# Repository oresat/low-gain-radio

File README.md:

# OreSat "Low Gain Radio" board

## Overview

The Low Gain Radio module is part of the sputnik capstone project and is the communications pipeline for the CubeSat.  

The module is centered around a microcontroller with an integrated transceiver and RF front end. Commands will be sent and received through this module. In most cases the system controller will assist in executing those commands. Communication with the system controller is done via a UART connection between the two modules.

## Main Topics
[Parts Selection](https://github.com/oresat/low-gain-radio/blob/master/docs/Parts_Selection.md#parts-selection-for-low-gain-radio)  
[Bill of Materials](https://github.com/oresat/low-gain-radio/blob/master/docs/low-gain-radio_BOM.xlsx)  
[Eagle Schematic](https://github.com/oresat/low-gain-radio/blob/master/eagle/low-gain-radio.sch)    
[Eagle Layout](https://github.com/oresat/low-gain-radio/blob/master/eagle/low-gain-radio.brd)    
[Test Plan](https://github.com/oresat/low-gain-radio/blob/master/docs/Test_Plan_Sputnik_Capstone.md#sputnik-capstone-test-plan)    

## Contents

datasheets - datasheets for components used

docs - documentation

eagle - contains Schematic and PCB layout for the Low Gain Radio

tools - contains firmware and tools for compiling/debugging

## Project team

Industry Sponsor: Andrew Greenberg (adg@ece.pdx.edu)

Faculty Advisor: Dr. Christof Teuscher (teuscher@pdx.edu)

* Capstone Team
* 
    * Jake Heath (jakeheath@gmail.com)

    * Shan Quinney (quinney@pdx.edu) 

    * William Harrington (wrh2@pdx.edu)

    * Mike Mathis (mdmathis@gmail.com)

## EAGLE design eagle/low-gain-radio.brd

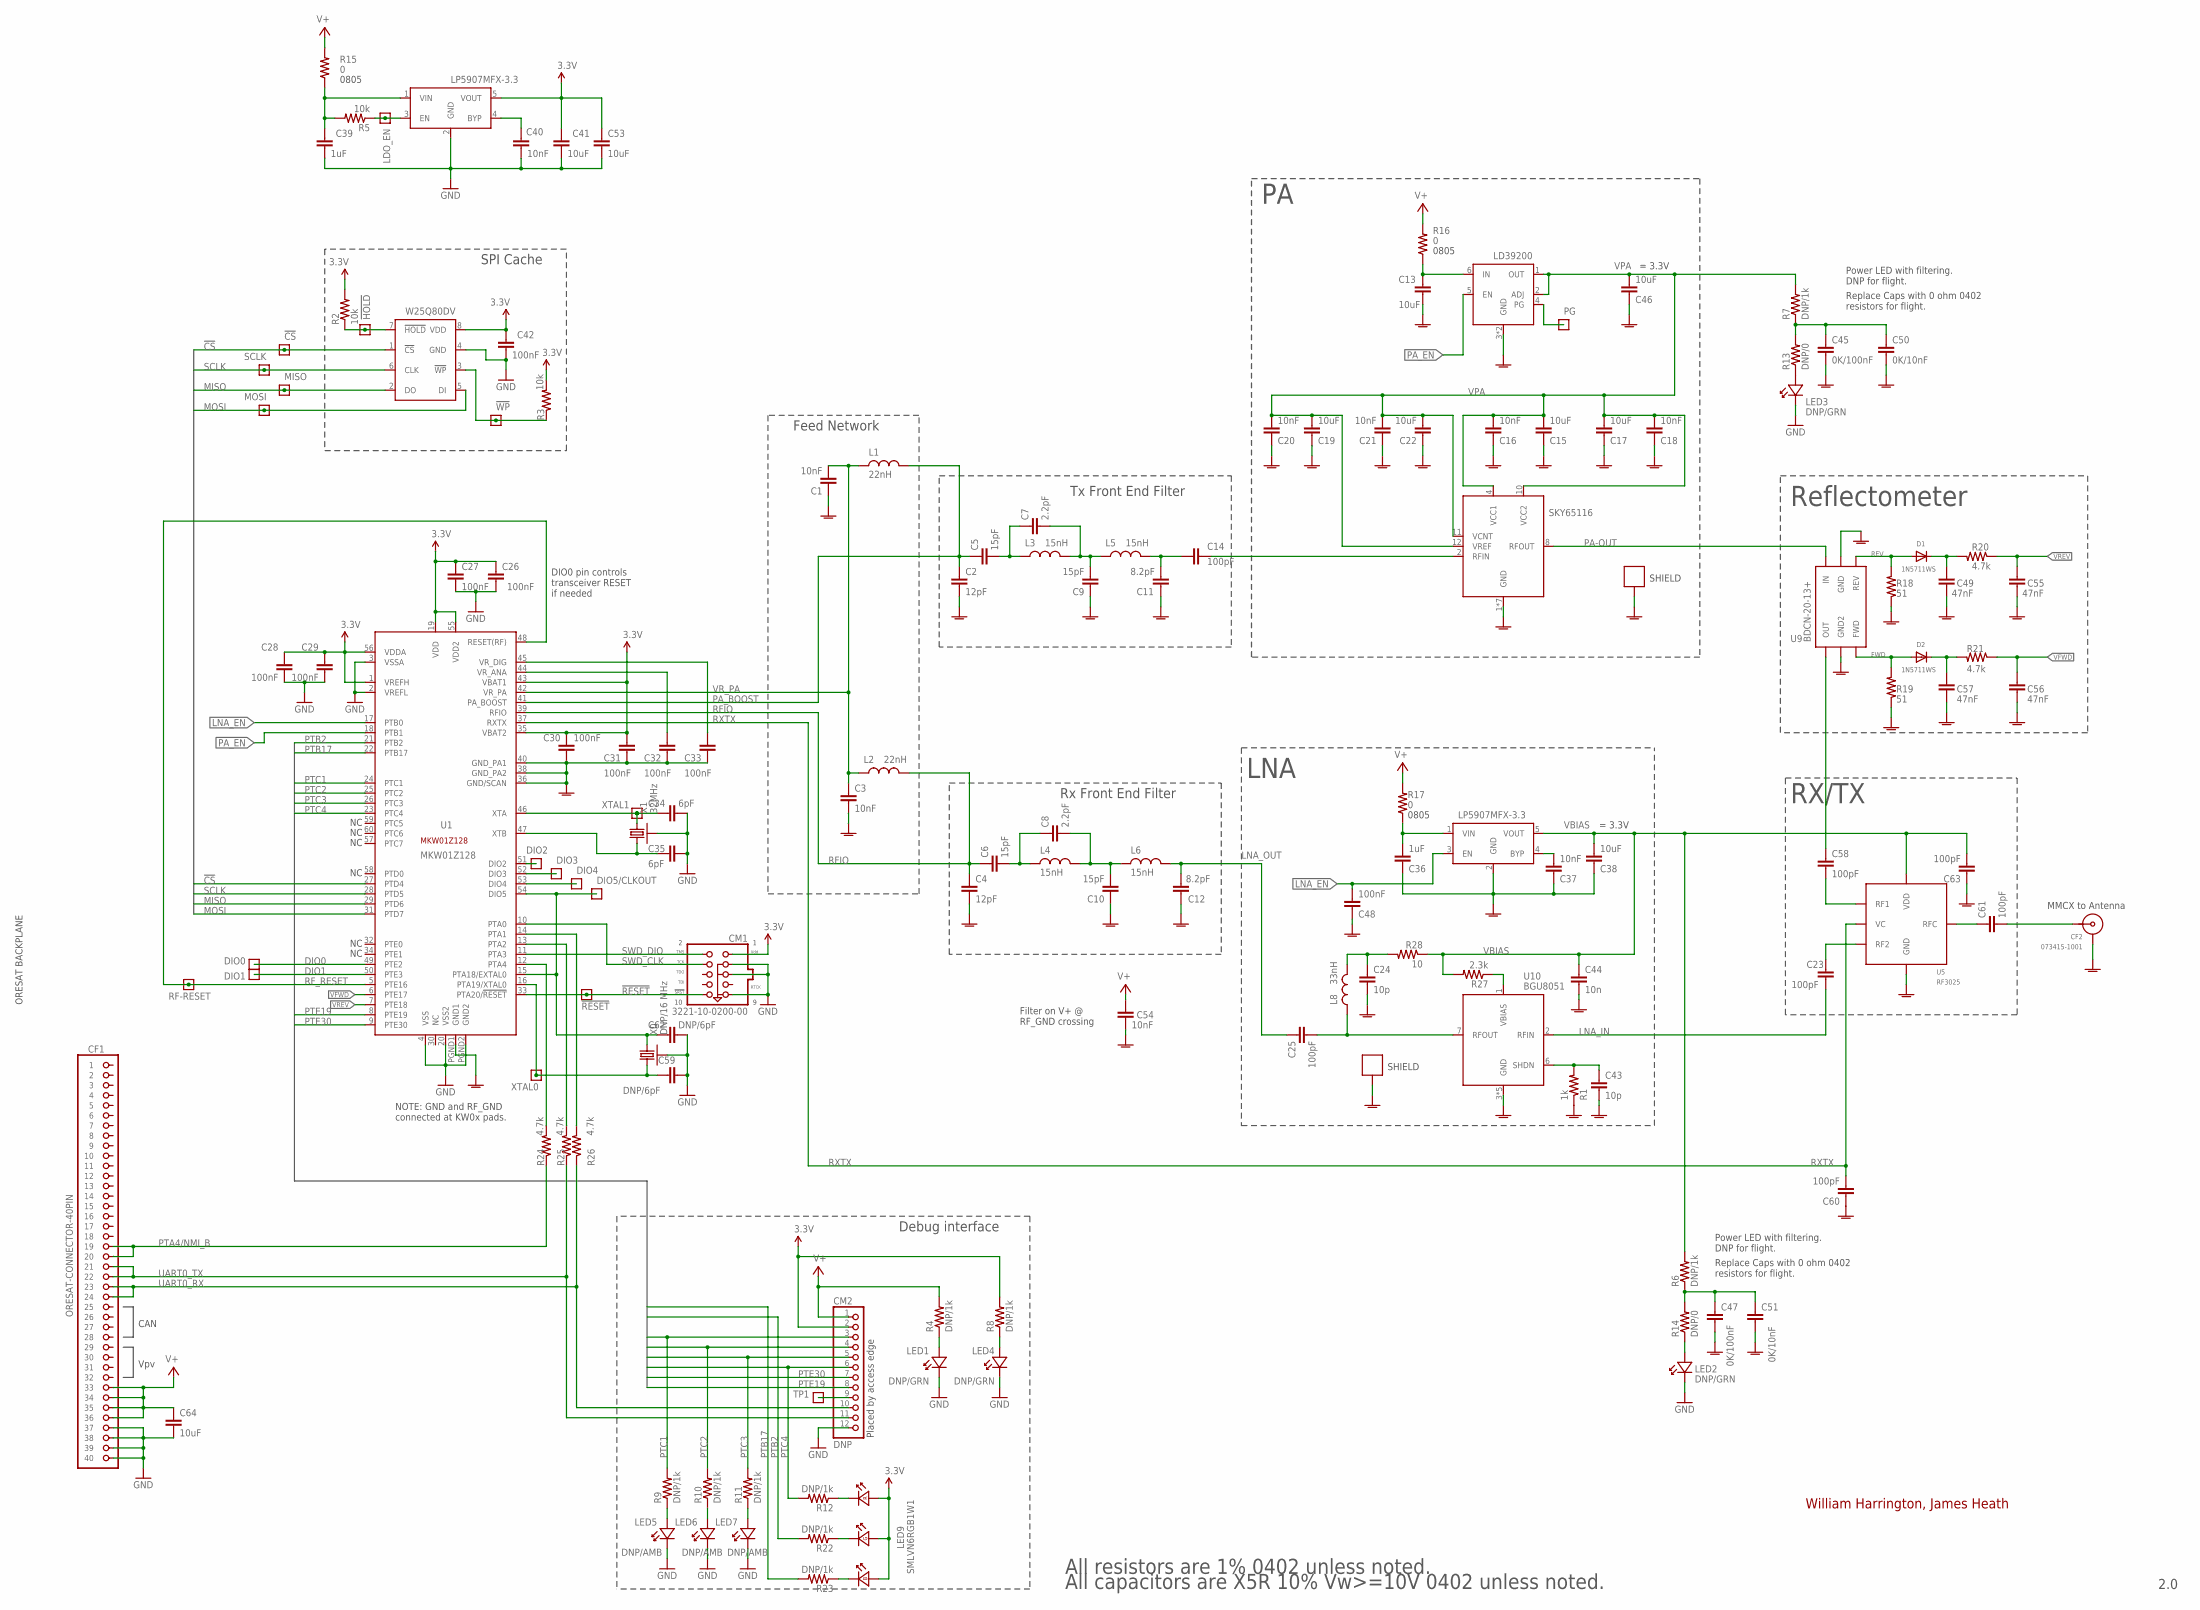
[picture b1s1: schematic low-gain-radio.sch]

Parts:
!CS: TEST-POINT; 2MM-TEST-POINT
!HOLD: TEST-POINT; 2MM-TEST-POINT
!RESET: TEST-POINT; 2MM-TEST-POINT
!WP: TEST-POINT; 2MM-TEST-POINT
C1, C3, C16, C18, C20, C21, C37, C40: 10nF; .0402-B-NOSILK; MPN GRM188R71H103KA01D
C2, C4: 12pF; .0402-B-NOSILK; MPN GRM1885C1H120JA01D
C5, C6, C9, C10: 15pF; .0402-B-NOSILK; MPN GRM1885C1H150JA01D
C7, C8: 2.2pF; .0402-B-NOSILK; MPN GRM1885C1H2R2CA01D
C11, C12: 8.2pF; .0402-B-NOSILK; MPN 06031U8R2BAT2A
C13, C15, C17, C19, C22, C38, C41, C46: 10uF; .0603-B-NOSILK; MPN GRM188R60J106ME47J
C14: 100pF; .0402-B-NOSILK; MPN 06035C104JAT2A
C23, C58, C60, C61, C63: 100pF; .0402-B-NOSILK; MPN CBR04C101F3GAC
C24, C43: 10p; .0402-B-NOSILK; MPN GRM155R71H102KA01D
C25: 100pF; .0402-B-NOSILK; MPN GRM155R71H102KA01D
C26, C27, C28, C29, C30, C31, C32, C33, C42, C48: 100nF; .0402-B-NOSILK; MPN 06035C104JAT2A
C34, C35: 6pF; .0402-B-NOSILK; MPN GQM1875C2E6R0BB12D
C36, C39: 1uF; .0603-B-NOSILK; MPN GRM188R61A105KA61D
C44: 10n; .0402-B-NOSILK; MPN GRM155R71H103KA88D
C45, C47: 0K/100nF; .0402-B-NOSILK; MPN 06035C104JAT2A
C49, C55, C56, C57: 47nF; .0402-B-NOSILK; MPN LMK105SD472KV-F
C50, C51: 0K/10nF; .0402-B-NOSILK; MPN GRM155R71H102KA01D
C53, C64: 10uF; .0805-B-NOSILK; MPN GRM188R60J106ME47J
C54: 10nF; .0402-B-NOSILK; MPN GRM155R71H102KA01D
C59, C62: DNP/6pF; .0402-B-NOSILK; MPN GQM1875C2E6R0BB12D
CF1: ORESAT-CONNECTOR-40PIN; HARWIN-ARCHER-M50-3202045; MPN M50-3202045
CF2: 073415-1001; CON-MMCX-F-MOLEX-0734151001; MPN 073415-1001
CM1: 3221-10-0200-00; PINHEADER-2X5-0.5+POL+RA+SILK; MPN 3221-10-0200-00
CM2: DNP; 1X12; MPN 68016-112HLF
D1, D2: 1N5711WS; SOD-323; MPN 1N5711WS
DIO0, DIO1, DIO2, DIO3, DIO4, DIO5/CLKOUT: TEST-POINT; 2MM-TEST-POINT
L1, L2: 22nH; .0402-B-NOSILK$1; MPN LQW18AN22NG00D
L3, L4, L5, L6: 15nH; .0402-B-NOSILK$1; MPN LQW18AN15NG00D
L8: 33nH; .0402-B-NOSILK$1; MPN LQW18AN82NG00D
LDO_EN: TEST-POINT; 2MM-TEST-POINT
LED1, LED2, LED3, LED4: DNP/GRN; LED-0603; MPN LTST-C191KGKT
LED5, LED6, LED7: DNP/AMB; LED-0603; MPN LTST-C191AKT
LED9: SMLVN6RGB1W1; LED-3528; MPN SMLVN6RGB1W1
MISO: TEST-POINT; 2MM-TEST-POINT
MOSI: TEST-POINT; 2MM-TEST-POINT
PG: TEST-POINT; 2MM-TEST-POINT
R1: 1k; .0402-B-NOSILK$1; MPN RC0603FR-071KL
R2, R3, R5: 10k; .0402-B-NOSILK$1; MPN RC0603FR-0710KL
R4, R6, R7, R8, R9, R10, R11, R12, R22, R23: DNP/1k; .0402-B-NOSILK$1; MPN RC0603FR-071KL
R13, R14: DNP/0; .0402-B-NOSILK$1; MPN RC0603JR-070RL
R15, R16, R17: 0; .0805-C-NOSILK$1; MPN RC0805JR-070RL
R18, R19: 51; .0402-B-NOSILK$1; MPN RC0402FR-0751RL
R20, R21: 4.7k; .0402-B-NOSILK$1; MPN RT0402BRD0721KL
R24, R25, R26: 4.7k; .0402-B-NOSILK$1; MPN RC0603FR-0710KL
R27: 2.3k; .0402-B-NOSILK$1; MPN RC0603FR-071KL
R28: 10; .0402-B-NOSILK$1; MPN RC0603FR-071KL
RF-RESET: TEST-POINT; 2MM-TEST-POINT
SCLK: TEST-POINT; 2MM-TEST-POINT
SH1, SH2: BMI-S-202-SHIELD; BMI-S-202
TP1: TEST-POINT; 2MM-TEST-POINT
U1: MKW01Z128; MPN MKW01Z128CHN
U2: SKY65116; MPN SKY65116-21
U3: W25Q80DV; MPN W25Q80DVSSIG
U4, U6: LP5907MFX-3.3; SOT23-5; MPN LP5907MFX-3.3
U5: RF3025; QFN-16_3MMX3MM; MPN RF3025TR7
U7: LD39200; MPN LD39200PU33R
U9: BDCN-20-13+; FV1206-1; MPN BDCN-20-13+
U10: BGU8051; IC_NXP_SOT1327-1
X0: DNP/16 MHz; CRYSTAL_2.5X2
X1: 32MHz; CRYSTAL_2.5X2
XTAL0, XTAL1: TEST-POINT; 2MM-TEST-POINT

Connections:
3.3V: C26.1, C27.1, C28.2, C29.2, C30.2, C31.2, C41.2, C42.2, C53.1, CM1.1 (VDD), CM2.2, LED9.1 (A), LED9.2 (A), LED9.3 (A), R2.2, R3.2, R8.2, U1.1 (VREFH), U1.19 (VDD), U1.35 (VBAT2), U1.43 (VBAT1), U1.55 (VDD2), U1.56 (VDDA), U3.8 (VDD), U4.5 (VOUT)
!CS: !CS.1, U1.27 (PTD4), U3.1 (!CS)
!HOLD: !HOLD.1, R2.1, U3.7 (!HOLD)
!RESET: !RESET.1, CM1.10 (SRST), U1.33 (PTA20/!RESET)
!WP: !WP.1, R3.1, U3.3 (!WP)
BYPASS: C37.2, U6.4 (BYP)
DIO0: DIO0.1, U1.49 (PTE2)
DIO1: DIO1.1, U1.50 (PTE3)
DIO2: DIO2.1, U1.51 (DIO2)
DIO3: DIO3.1, U1.52 (DIO3)
DIO4: DIO4.1, U1.53 (DIO4)
EXTAL0: C62.2, DIO5/CLKOUT.1, U1.15 (PTA18/EXTAL0), U1.54 (DIO5), X0.3 (2)
FWD: D2.A, R19.2, U9.6 (FWD)
GND: C26.2, C27.2, C28.1, C29.1, C34.1, C35.1, C39.1, C40.1, C41.1, C42.1, C53.2, C59.1, C62.1, C64.2, CF1.P$37 (37), CF1.P$38 (38), CF1.P$39 (39), CF1.P$40 (40), CM1.3 (GND3), CM1.5 (GND5), CM1.9 (GND9), CM2.12, LED1.K, LED2.K, LED3.K, LED4.K, LED5.K, LED6.K, LED7.K, U1.2 (VREFL), U1.3 (VSSA), U1.4 (VSS), U1.20 (VSS2), U1.PGND2 (GND2), U3.4 (GND), U4.2 (GND), X0.2 (SHIELD), X0.4 (SHIELD), X1.2 (SHIELD), X1.4 (SHIELD)
LDO_EN: LDO_EN.1, R5.1, U4.3 (EN)
LNA_EN: C48.2, U1.17 (PTB0), U6.3 (EN)
LNA_IN: C23.1, U10.2 (RFIN)
LNA_IN_DC: C23.2, U5.13 (RF2)
LNA_OUT: C12.2, C25.1, L6.2
LNA_OUT_DC: C25.2, L8.1, U10.7 (RFOUT)
LNA_SHDN: C43.1, R1.2, U10.6 (SHDN)
LNA_VBIAS: R27.1, U10.1 (VBIAS)
MISO: MISO.1, U1.29 (PTD6), U3.2 (DO)
MOSI: MOSI.1, U1.31 (PTD7), U3.5 (DI)
unnamed: LED3.A, R13.1
unnamed: LED2.A, R14.1
unnamed: PG.1, U7.4 (PG)
unnamed: CM2.9, TP1.1
unnamed: C13.2, R16.1, U7.6 (IN)
unnamed: C35.2, U1.47 (XTB), X1.1
unnamed: C36.2, R17.1, U6.1 (VIN)
unnamed: C5.2, C7.1, L3.1
unnamed: LED9.6 (K), R23.1
unnamed: C39.2, R5.2, R15.1, U4.1 (VIN)
unnamed: C40.2, U4.4 (BYP)
unnamed: LED1.A, R4.1
unnamed: LED5.A, R9.1
unnamed: C7.2, C9.2, L3.2, L5.1
unnamed: C11.2, C14.2, L5.2
unnamed: C6.2, C8.1, L4.1
unnamed: C8.2, C10.2, L4.2, L6.1
unnamed: LED6.A, R10.1
unnamed: LED7.A, R11.1
unnamed: LED4.A, R8.1
unnamed: LED9.4 (K), R22.1
unnamed: C49.1, D1.C, R20.2
unnamed: R26.2, U1.14 (PTA1)
unnamed: LED9.5 (K), R12.1
unnamed: R25.2, U1.13 (PTA2)
unnamed: C57.1, D2.C, R21.2
unnamed: C58.1, U9.4 (OUT)
unnamed: C61.2, CF2.CENTER
unnamed: C32.2, U1.44 (VR_ANA)
unnamed: R24.2, U1.12 (PTA4)
unnamed: C33.2, U1.45 (VR_DIG)
unnamed: C14.1, U2.2 (RFIN)
PA-OUT: U2.8 (RFOUT), U9.1 (IN)
PA_BOOST: C2.1, C5.1, L1.2, U1.41 (PA_BOOST)
PA_EN: U1.18 (PTB1), U7.5 (EN)
PA_IN: C58.2, U5.8 (RF1)
PTA4/NMI_B: CF1.P$19 (19), CF1.P$20 (20), R24.1
PTB2: R22.2, U1.21 (PTB2)
PTB17: R23.2, U1.22 (PTB17)
PTC1: CM2.3, R9.2, U1.24 (PTC1)
PTC2: CM2.4, R10.2, U1.25 (PTC2)
PTC3: CM2.5, R11.2, U1.26 (PTC3)
PTC4: CM2.6, R12.2, U1.23 (PTC4)
PTE19: CM2.8, U1.8 (PTE19)
PTE30: CM2.7, U1.9 (PTE30)
REV: D1.A, R18.2, U9.3 (REV)
RFIO: C4.1, C6.1, L2.2, U1.39 (RFIO)
RF_GND: C1.1, C2.2, C3.2, C4.2, C9.1, C10.1, C11.1, C12.1, C13.1, C15.1, C16.1, C17.1, C18.1, C19.1, C20.1, C21.1, C22.1, C24.2, C30.1, C31.1, C32.1, C33.1, C36.1, C37.1, C38.1, C43.2, C44.2, C45.1, C46.1, C47.1, C48.1, C49.2, C50.1, C51.1, C54.1, C55.2, C56.2, C57.2, C60.1, C63.1, CF2.G1 (SHIELD), CF2.G2 (SHIELD), CF2.G3 (SHIELD), CF2.G4 (SHIELD), R1.1, R18.1, R19.1, SH1.P$1, SH1.P$2, SH1.P$3, SH1.P$4, SH1.P$5, SH1.P$6, SH1.P$7, SH1.P$8, SH1.P$9, SH1.P$10, SH1.P$11, SH1.P$12, SH2.P$1, SH2.P$2, SH2.P$3, SH2.P$4, SH2.P$5, SH2.P$6, SH2.P$7, SH2.P$8, SH2.P$9, SH2.P$10, SH2.P$11, SH2.P$12, U1.36 (GND/SCAN), U1.38 (GND_PA2), U1.40 (GND_PA1), U1.PGND1 (GND1), U2.1 (GND), U2.3 (GND), U2.5 (GND), U2.6 (GND), U2.7 (GND), U2.9 (GND), U2.CENTER (GND), U5.1 (GND), U5.2 (GND), U5.4 (GND), U5.6 (GND), U5.7 (GND), U5.9 (GND), U5.10 (GND)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
RF_RESET: RF-RESET.1, U1.5 (PTE16), U1.48 (RESET(RF))
RXTX: C60.2, U1.37 (RXTX), U5.16 (VC)
RXTX_OUT: C61.1, U5.3 (RFC)
SCLK: SCLK.1, U1.28 (PTD5), U3.6 (CLK)
SWD_CLK: CM1.4 (TCK), U1.10 (PTA0)
SWD_DIO: CM1.2 (TMS), U1.11 (PTA3)
UART0_RX: CF1.P$23 (23), CF1.P$24 (24), CM2.10, R26.1
UART0_TX: CF1.P$21 (21), CF1.P$22 (22), CM2.11, R25.1
V+: C54.2, C64.1, CF1.P$33 (33), CF1.P$34 (34), CF1.P$35 (35), CF1.P$36 (36), CM2.1, R4.2, R15.2, R16.2, R17.2
VBIAS: C38.2, C44.1, C63.2, R6.2, R27.2, R28.1, U5.5 (VDD), U6.5 (VOUT)
VBIAS-R: C24.1, L8.2, R28.2
VFWD: C56.1, R21.1, U1.6 (PTE17)
VPA: C15.2, C16.2, C17.2, C18.2, C19.2, C20.2, C21.2, C22.2, C46.2, R7.2, U2.4 (VCC1), U2.10 (VCC2), U2.11 (VCNT), U2.12 (VREF), U7.1 (OUT), U7.2 (ADJ)
VREV: C55.1, R20.1, U1.7 (PTE18)
VR_PA: C1.2, C3.1, L1.1, L2.1, U1.42 (VR_PA)
V_LNA_FILTERED: C47.2, C51.2, R6.1, R14.2
V_PA_FILTERED: C45.2, C50.2, R7.1, R13.2
XTA: C34.2, U1.46 (XTA), X1.3 (2), XTAL1.1
XTAL0: C59.2, U1.16 (PTA19/XTAL0), X0.1, XTAL0.1

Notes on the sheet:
William Harrington, James Heath
Feed Network
Tx Front End Filter
Rx Front End Filter
LNA
RX/TX
MMCX to Antenna
SPI Cache
Debug interface
Placed by access edge
ORESAT BACKPLANE
DIO0 pin controls transceiver RESET if needed
= 3.3V
NOTE: GND and RF_GND connected at KW0x pads.
Power LED with filtering. DNP for flight.
Filter on V+ @ RF_GND crossing
Reflectometer
CAN
Vpv
SHIELD
All resistors are 1% 0402 unless noted.
0805
All capacitors are X5R 10% Vw>=10V 0402 unless noted.
2.0
Replace Caps with 0 ohm 0402 resistors for flight.

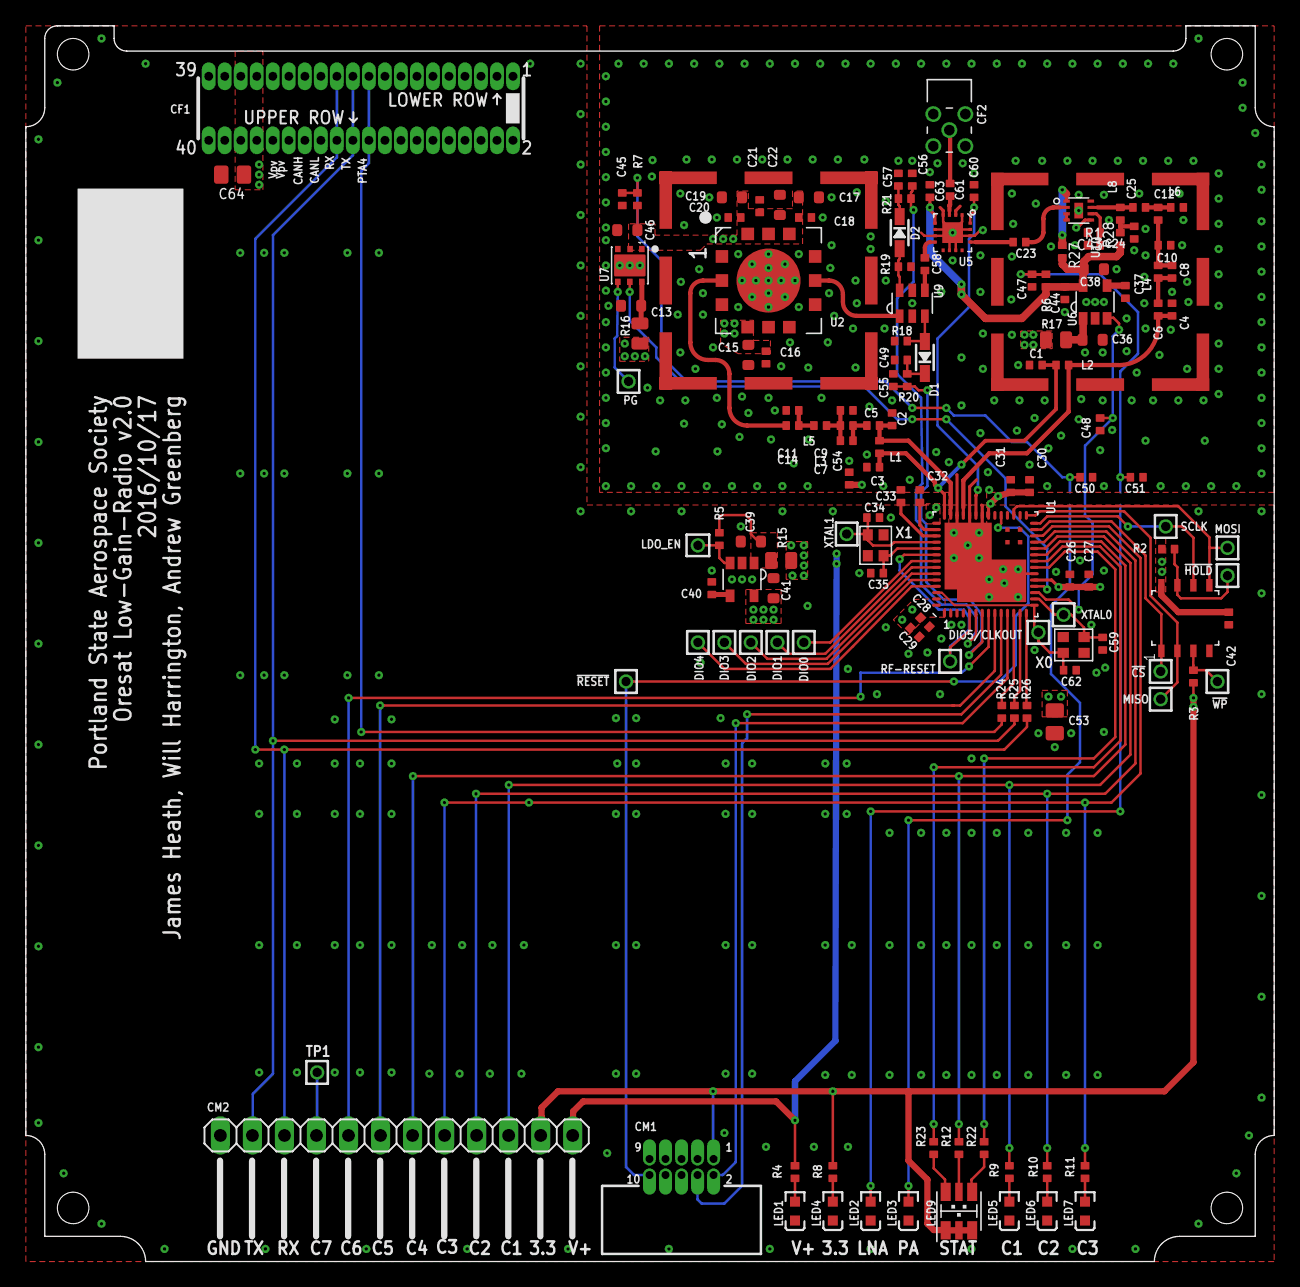
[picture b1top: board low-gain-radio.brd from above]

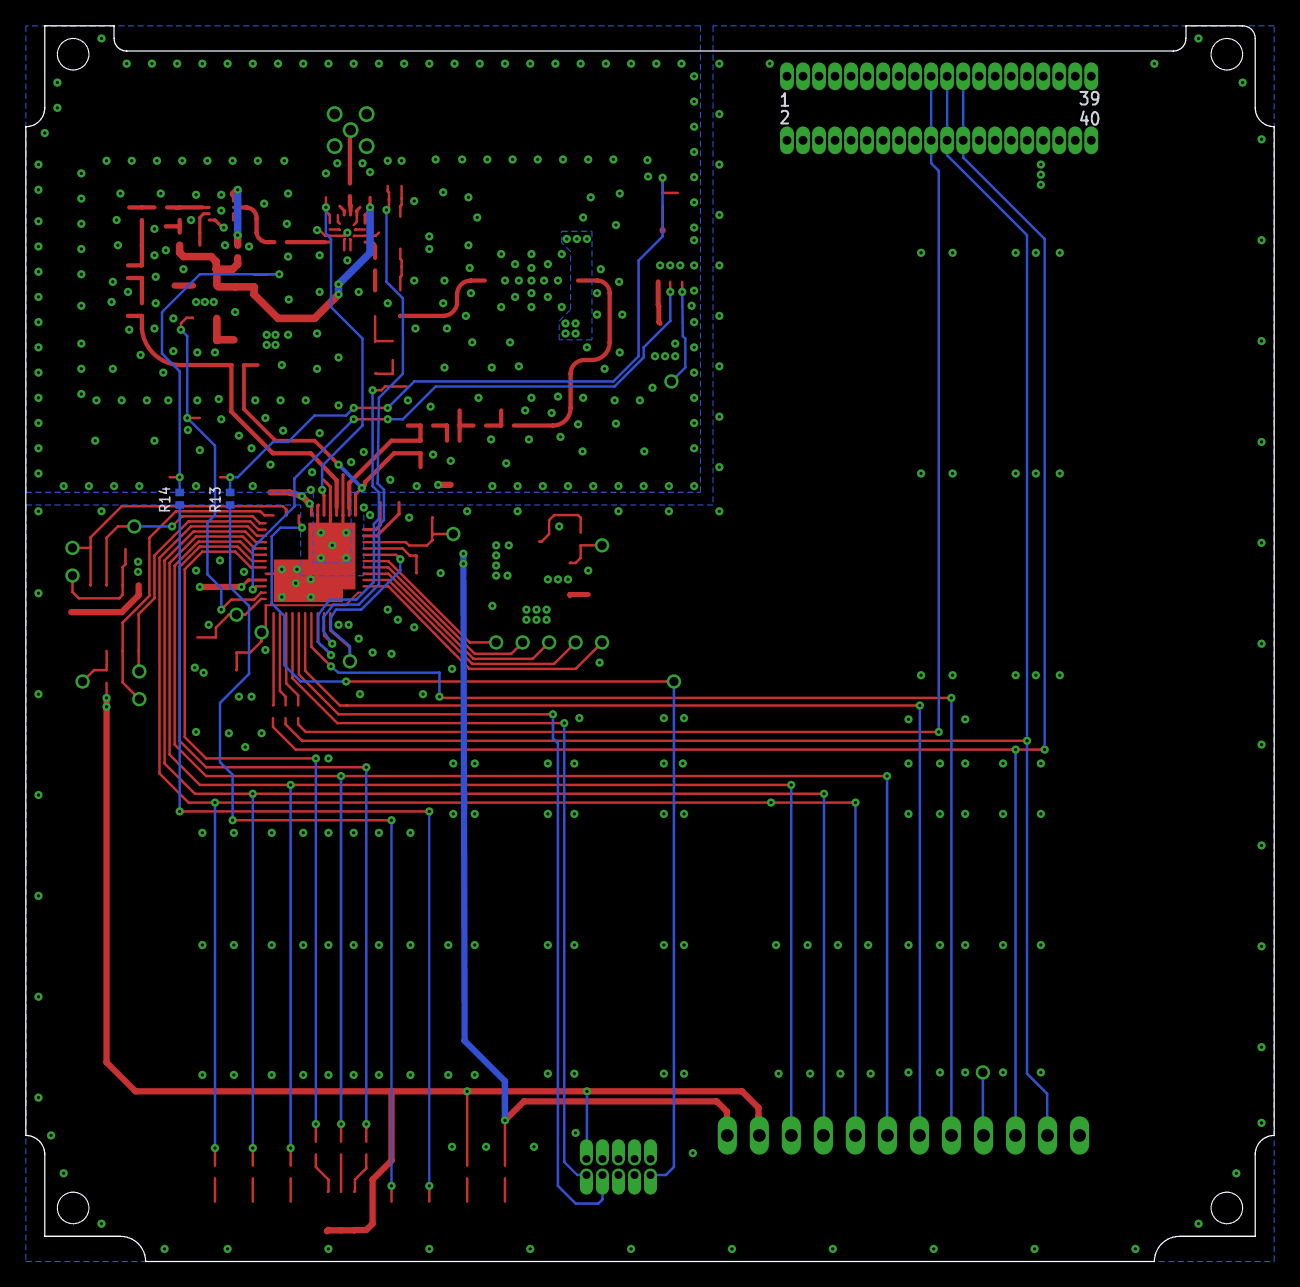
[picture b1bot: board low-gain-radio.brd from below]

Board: 4 copper layers, 99.0 x 98.0 mm, 145 parts (2 on the bottom side), 91 nets.

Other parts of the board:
U$35: ORESAT-CARD-V0.4

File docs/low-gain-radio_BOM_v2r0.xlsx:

Bill Of Materials for PSAS Low Gain Radio (LGR)
source file: low-gain-radio.sch
Variant: NA
PCB version 2.0
BOM revision 0 |  | P/DNP = | Place/Do Not Place (DNP is for final production boards)
Last Modified: 2016.10.17 |  | Generic = | Any generic part with the same characteristics are OK (e.g., bypass cap)
Qty | Part References | Mfg | Mfg PN | P/NP | Description | Value | Dist | Dist PN | Generic | NOTES
2 | C7, C8 | Murata | GJM1555C1H2R2BB01D | P | Capacitor, 0402, 2.2pF 50V Ceramic C0G, NP0 ±0.1pF | 2.2pF | Digi-Key | 490-8092-1-ND | N
2 | C34, C35 | Murata | GRM1555C1H6R0DA01D | P | Capacitor, 0402, 6pF 50V Ceramic C0G, NP0 ±0.5pF | 6pF | Digi-Key | 490-5877-1-ND | Y | Cystal caps
2 | C59, C62 | Murata | GRM1555C1H6R0DA01D | NP | Capacitor, 0402, 6pF 50V Ceramic C0G, NP0 ±0.5pF | 6pF | Digi-Key | 490-5877-1-ND | Y | Cystal caps
2 | C11, C12 | Murata | GJM1555C1H8R2BB01D | P | Capacitor, 0402, 8.2pF 50V Ceramic C0G, NP0 ±0.1pF | 8.2pF | Digi-Key | 490-11240-1-ND | N
2 | C2, C4 | Murata | GJM1555C1H120FB01D | P | Ceramic, 0402, 12pF 50V C0G, NP0 ±1% | 12pF | Digi-Key | 490-11190-1-ND | N
4 | C5, C6, C9, C10 | Murata | GJM1555C1H150FB01D | P | Ceramic, 0402, 15pF 50V C0G, NP0 ±1% | 15pF | Digi-Key | 490-11191-1-ND | N
7 | C14, C23, C25, C58, C60, C61, C63 | Kemet | CBR04C101F3GAC | P | Capacitor, 0402, 100pF 25V Ceramic C0G, NP0 | 100pF | Digi-key | 399-11246-2-ND | N
1 | C24 | Murata | GRM155R71H102JA01J | P | Capacitor , 0402, 1000pF 50V Ceramic X7R ±5% | 1nF | Digi-key | 490-6349-1-ND | Y
10 | C1, C3, C16, C18, C20, C21, C37, C40, C44, C54 | Murata | GRM155R71H103JA88D | P | Capacitor, 0402, 10000pF 50V Ceramic X7R ±5% | 10nF | Digi-Key | 490-7763-1-ND | Y
2 | C50, C51 | Murata | GRM155R71H103JA88D | NP | Capacitor, 0402, 10000pF 50V Ceramic X7R ±5% | DNP/10nF | Digi-key | 490-7763-1-ND | Y
4 | C49, C55, C56, C57 | Murata | GRM155R71H473KE14D | P | Capacitor, 0402, 0.047µF 50V Ceramic X7R ±10% | 47nF | Digi-key | 490-10702-1-ND | Y
12 | C26, C27, C28, C29, C30, C31, C32, C33, C42, C48 | Murata | GRM155R71H104KE14J | P | Capacitor, 0402, 0.10µF 50V Ceramic X7R ±10% | 100nF | Digi-Key | 490-13342-1-ND | Y
2 | C45, C47 | Murata | GRM155R71H104KE14J | NP | Capacitor, 0402, 0.10µF 50V Ceramic X7R ±10% | DNP/100nF | Digi-Key | 478-5778-1-ND | Y
2 | C36, C39 | Murata | GRM188R61A105KA61D | P | Capacitor, 0603, 1µF 10V Ceramic X5R | 1uF | Digi-Key | 490-1543-2-ND | Y
10 | C13, C15, C17, C19, C22, C38, C41, C46, C53, C64 | Murata | GRM188R61C106MA73D | P | Capacitor, 0603, 10µF 16V Ceramic X5R | 10uF | Digi-Key | 490-7201-1-ND | Y
1 | C43 | AVX | TAJC107K010RNJ | P | Capacitor, 2312, 100µF Molded Tantalum 10V 1.2 Ohm | 100uF | Digi-Key | 478-1704-1-ND | Y
1 | CF1 | Harwin Archer | M50-3202045 | P | 40 pos. Receptacle 1.27mm Through Hole, Right Angle, Gold | - | Digi-Key | 952-1381-5-ND | N
1 | CF2 | Molex | 073415-1001 | P | MMCX, Female, Through Hole, RA, Gold | - | Digi-Key | WM5552-ND | Y | CHANGED FROM V1.2
1 | CM1 | CNC Tech | 3221-10-0200-00 | P | ARM JTAG Conn.: 10 pos. Header, Shrouded Connector 1.27mm RA Gold | - | Digi-Key | 1175-1627-ND | Y | CHANGED FROM V1.2
1 | CM2 | Amphenol | 68016-112HLF | NP | Debug Conn.: 12 pos. Unshrouded Connector 2.54mm Right Angle Gold | - | Digi-Key | 609-3316-ND | Y | CHANGED FROM V1.2
2 | D1, D2 | Diodes Incorporated | 1N5711WS | P | RF Diode Schottky - Single 70V 15mA 333mW SOD-123 | - | Digi-key | 1N5711WS-FDICT-ND | Y
2 | L1, L2 | Murata | LQW15AN22NG80D | P | Inductor, 0402, 22nH Unshielded Wirewound 780mA 202 mOhm ±2% | - | Digi-Key | 490-7628-1-ND | N | CHANGED FROM V1.2
4 | L3, L4, L5, L6 | Murata | LQW15AN15NG00D | P | Inductor, 0402, 15nH Unshielded Wirewound 460mA 160 mOhm ±2% | - | Digi-Key | 490-6771-1-ND | N | CHANGED FROM V1.2
1 | L8 | Murata | LQW15AN82NG00D | P | Inductor, 0402, 82nH Unshielded Wirewound 130mA 2.24 Ohm ±2% | - | Digi-Key | 490-6848-1-ND | N | CHANGED FROM V1.2
4 | LED1, LED2, LED3, LED4 | Lite-On Inc. | LTST-C191KGKT | NP | Green 571nm LED Indication - Discrete 2V 0603 | - | Digi-Key | 160-1446-1-ND | Y
3 | LED5, LED6, LED7 | Lite-On Inc. | LTST-C191AKT | NP | Amber 602nm LED Indication - Discrete 2.1V 0603 | - | Digi-Key | 160-1440-1-ND | Y
1 | LED9 | Rohm | SMLVN6RGB1W1 | NP | RGB LED with separate contacts for all 3 chips | - | Digi-Key | 846-1187-1-ND | N | NEW
2 | R13, R14 | Yageo | RC0402FR-070RL | NP | Resistor, 0402, 0.0 OHM JUMPER 1/16W | 0 | Digi-Key | 311-0.0LRCT-ND | Y | CHANGED FROM V1.2
3 | R15, R16, R17 | Yageo | RC0805JR-070RL | P | Resistor, 0805, 0.0 OHM JUMPER 1/8W | 0 | Digi-key | 311-0.0ARCT-ND | Y | NEW
2 | R18, R19 | Yageo | RC0402FR-0751RL | P | Resistor, 0402, 51 OHM 1% 1/16W | 51 | Digi-key | 311-51.0LRCT-ND | Y | NEW
1 | R1 | Samsung | RC1608F2490CS | P | Resistor, 0603, 249 OHM 1% 1/10W | 250 | Digi-Key | 1276-4592-2-ND | Y
10 | R4, R6, R7, R8, R9, R10, R11, R12, R22, R23 | Yageo | RT0402FRE071KL | NP | Resistor, 0402, 1K OHM 1% 1/16W | 1k | Digi-Key | YAG1234CT-ND | Y | CHANGED FROM V1.2
2 | R20, R21 | Yageo | RT0402FRE074K7L | P | Resistor, 0402, 4.7K OHM 1% 1/16W | 4.7k | Digi-key | YAG3347CT-ND | Y | NEW
3 | R2, R3, R5 | Yageo | RT0402FRE0710KL | P | Resistor, 0402, 10K OHM 1% 1/16W | 10k | Digi-Key | YAG1233CT-ND | Y | CHANGED FROM V1.2
2 | SH1, SH2 | Laird Technologies EMI | BMI-S-202-F | P | RF Shield Frame 16.50mm x 16.50mm | - | Digi-Key | 903-1051-1-ND | N
2 | SH1, SH2 | Laird Technologies EMI | BMI-S-202-C | P | RF Shield Cover 16.50mm X 16.50mm,Vent Holes,Snap Fit | - | Digi-Key | 903-1014-ND | N
1 | U1 | NXP | MKW01Z128CHN | P | IC RF TxRx + MCU General ISM < 1Ghz 60-VFLGA | - | Digi-Key | MKW01Z128CHN-ND | N
1 | U2 | Skyworks | SKY65116-21 | P | PA: RF Amplifier IC 35 dBm 390Mhz ~ 500Mhz 12-MCM (8.4x8.4) | - | Digi-Key | 863-1072-1-ND | N
1 | U3 | Winbond Electronics | W25Q80DVSSIG | P | IC FLASH 8MBIT 104MHZ 8SOIC | - | Digi-Key | W25Q80DVSSIG-ND | N
2 | U4, U6 | Texas Instruments | LP5907MFX-3.3 | P | Linear Voltage Regulator IC Positive Fixed 1 Output 3.3V 250mA SOT-23 | - | Digi-Key | 296-38557-1-ND | N
1 | U5 | RFMD | RF3025TR7 | P | RF Switch IC 802.11b/g SPDT 6GHz 50 Ohm 16-QFN (3x3) | - | Digi-Key | 689-1087-1-ND | N | CHANGED FROM V1.2
1 | U7 | STMicroelectronics | LD39200PU33R | P | Linear Voltage Regulator IC Positive Fixed 1 Output 3.3V 2A 6-DFN (3x3) | - | Digi-Key | 497-15229-2-ND | N
1 | U8 | M/A-Com | MAAL-010704-TR3000 | P | LNA: RF Amplifier IC General Purpose 100Mhz ~ 3.5Ghz SC-70-6 (SOT-363) | - | Digi-Key | 1465-1261-1-ND | N | CHANGED FROM V1.2??????
1 | U9 | Mini-Circuits | BDCN-20-13+ | P | High power bi-directional coupler 50Ω 20 dB Coupling 360 to 1000 Mhz | - | Mini-Circuits | BDCN-20-13+ | N | NEW
1 | X0 | EPSON | FA-20H 16.0000MF10Z-AJ0 | NP | 16Mhz ±10ppm Crystal 8pF 80 Ohm -20°C ~ 75°C 4-SMD | - | Digi-Key | SER4068CT-ND | Y | NEW
1 | X1 | ECS | ECS-320-8-36CKM-TR | P | 32Mhz ±10ppm Crystal 8pF 50 Ohm -20°C ~ 70°C 4-SMD | - | Digi-Key | XC1563CT-ND | Y | CHANGED FROM V1.2

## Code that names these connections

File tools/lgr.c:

/*
	Low Gain Radio firmware

	Programmed by William Harrington
*/
#include "transceiver.h"
#include "clksetup.h"
#include "uart.h"

#define PAYLOAD_READY_MASK 0x04

/* LNA Enable */
#define PTB0 (1 << 0)

/* PA Enable */
#define PTB1 (1 << 1)

/* RF Reset */
#define PTE2 (1 << 2)

/* LED5 */
#define PTC1 (1 << 1)

/* LED6 */
#define PTC2 (1 << 2)

/* LED7 */
#define PTC3 (1 << 3)

/* LED8 */
#define PTC4 (1 << 4)

/* alternative function number */
#define pin_disable (0 << 8)
#define alt1 (1 << 8)
#define alt2 (2 << 8)
#define alt3 (3 << 8)
#define alt4 (4 << 8)
#define alt5 (5 << 8)
#define alt6 (6 << 8)
#define alt7 (7 << 8)

void initialize_gpio(void){

	/* port B pins */
	PORTB.PCR[0] |= alt1;
	PORTB.PCR[1] |= alt1;

	/* port C pins */
	PORTC.PCR[1] |= alt1;
	PORTC.PCR[2] |= alt1;
	PORTC.PCR[3] |= alt1;
	PORTC.PCR[4] |= alt1;

	PORTE.PCR[2] |= alt1;

	/* set data direction as output */
	GPIOB.PDDR |= PTB1 | PTB0;
	GPIOC.PDDR |= PTC4 | PTC3 | PTC2 | PTC1;
	GPIOE.PDDR |= PTE2;

	GPIOE.PCOR = PTE2;
	return;
}

void initialize_uart0(void){
	/* UART0 configuration */
	struct uart_config myUART = {
		/* pin for transmit = PTA2 */
		.TX = {.port=&PORTA, .pin=2,},

		/* pin for receive = PTA1 */
		.RX = {.port=&PORTA, .pin=1,},

		/* baud rate */
		.baud = 9600,
	};
	uart_init(&UART0, &myUART);
}

int main(void) {
	/* check transceiver mode */
	uint8_t trans_mode = Mode_TX;
	

	/* call initialization procedures */
	initialize_clock();
	initialize_gpio();
	initialize_uart0();

	

	/* Due to a hardware error, DIO0 is hooked to RF reset, but goes high on 
	 * packet transmit, leading to as soon as the transmitter starting to send
	 * it resets itself
	 */
	uint8_t DIOMapping = 0x80;
	trans_write_register(transceiver.RegDioMapping1, &DIOMapping, 1);

	
	
	static uint8_t standby = 0x4;

	if(trans_mode == Mode_TX){
		/* enable PA */
		GPIOB.PTOR = PTB1;
		/* Enable LNA in order to power inverter on rx/tx switch*/
		GPIOB.PTOR = PTB0;

		configure_transceiver(Mode_TX, PAOutputCfg(PA1, 0));
		/* Enter standby mode*/
		trans_write_register(transceiver.RegOpMode, &standby, 1); 

		
    }
	if(trans_mode == Mode_RX){
		/* Enable LNA */
		GPIOB.PTOR = PTB0;
		/* Enter receive mode */
		trans_write_register(transceiver.RegOpMode, &trans_mode, 1); 
		/* this function is in transceiver.c if you want more details */

		configure_transceiver(Mode_RX, PAOutputCfg(0, 0));
    }

    /*

	Be sure that trans_mode is Mode_RX or Mode_TX so that the appropriate
	branch is taken in the while loop. The actual opmode may be different.
		
    */
    
	uint8_t tx = 0x44;
	static uint8_t rx[PACKET_LENGTH];
	
	uint8_t alive = 0x7;
	uint8_t sleep = 0x4;
	
	static uint8_t payload_ready[2];

	static uint8_t txbytes[] = {0x01, 0x23, 0x45, 0x67, 0x89, 0xAB, 0xCD};

	static uint8_t test = 0;
	static uint8_t one = 0x1;

/*

	while(1){

		for(uint32_t i = 0; i < 500000; ++i){
			trans_read_register(transceiver.RegIrqFlags1, &test, 1);
			if (test & 0x8){
				GPIOC.PSOR = PTC2;
			}
			else{
				GPIOC.PCOR = PTC2;
			}
		}

		trans_write_register(transceiver.RegRssiConfig, &one, 1);
		uint8_t rssi_done = 0;
		while (!(rssi_done & 0x2)){
			trans_read_register(transceiver.RegRssiConfig, &rssi_done, 1);
		}
		trans_read_register(transceiver.RegRssiValue, &test, 1);
		if (test){
		GPIOC.PTOR = PTC2;
		}
	}*/
	

	


	while(1) {
		

		/* transmit byte if in TX mode */
		if(trans_mode == Mode_TX){

			/* write to transceiver fifoe to transmit data */
			trans_write_register(transceiver.RegFifo, txbytes, PACKET_LENGTH);
			
			
			/* blink status LED */
			GPIOC.PTOR = PTC1;
			for(uint32_t i = 0; i < 5000000; ++i);
			/* transmit byte written over UART for debugging */
			//uart_write(&UART0, 1, &tx);
        }

		/* check fifo for received bytes in RX mode */
		if(trans_mode == Mode_RX){
			uart_write(&UART0, 1, &alive); //I'm alive signal for the sys controller
				

			

			for(uint32_t i = 0; i < 500000; ++i);	
			
			/* blink status LED */
			GPIOC.PTOR = PTC4;

			/*Check if the payload is ready*/
			trans_read_register(transceiver.RegIrqFlags1, payload_ready, 2);

			//trans_read_register(transceiver.RegRssiValue, &trans_mode, 1);

			if (payload_ready[1] & 0x40){
				GPIOC.PSOR = PTC1;
			}
			else{
				GPIOC.PCOR = PTC1;
			}

			if (payload_ready[1] & 0x04){
				GPIOC.PSOR = PTC2;
			}
			else{
				GPIOC.PCOR = PTC2;
			}


			
			if (payload_ready[1] & 0x04){

				/* read transceiver fifo to grab received data */
				trans_read_register(transceiver.RegFifo, rx, PACKET_LENGTH);	
				/* Write the packet received out to UART */
				uart_write(&UART0, PACKET_LENGTH, rx);		
				/* Packet received LED toggle */
				GPIOC.PTOR = PTC3;
			}
        }
	}
	return 0;
}

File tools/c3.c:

/*
	Example code of lighting LEDs on c3 board

	Programmed by William Harrington, Michael Mathis, and Theo Hill
 */
#include "drivers/uart.h"
#include "drivers/transceiver.h"
#include "drivers/spi.h"

/* System clock gating control */
#define SCGC_SPI1_CLK (1 << 23)
#define SCGC_SPI0_CLK (1 << 22)
#define SCGC_SPI_CLK_OFF 0xFF3FFFFF
#define SCGC_PORTA_CLK (1 << 9)
#define SCGC_PORTB_CLK (1 << 10)
#define SCGC_PORTC_CLK (1 << 11)
#define SCGC_PORTD_CLK (1 << 12)
#define SCGC_PORTE_CLK (1 << 13)
#define SCGC_PORTAE_CLK (31 << 9)
#define SCGC_PORTAE_CLK_OFF 0xFFFFC1FF

/* Reference clock control */
#define CLK_DIVIDE_0 0x0
#define CLK_DIVIDE_16 (1 << 2)

#if 1
void initialize_spi(void){
	/* enable clock for SPI modules */
	SIM.SCGC4 |= SCGC_SPI1_CLK | SCGC_SPI0_CLK;

	/* enable clock for all ports */
	SIM.SCGC5 |= SCGC_PORTAE_CLK;

	/* The transceiver requires a specific SPI configuration*/
	initialize_trans_spi(&SPI0);

	/* Send to transceiver to divide clock signal on PTA18 */
	uint8_t RegDioMapping2Cfg = CLK_DIVIDE_0;
	//uint8_t RegDioMapping2Cfg = CLK_DIVIDE_16;
	trans_write_register(transceiver.RegDioMapping2, &RegDioMapping2Cfg, 1);

	/* disable the clocks we enabled for this as we are going to mess with the clock settings now */
	SIM.SCGC4 &= SCGC_SPI_CLK_OFF;
	SIM.SCGC5 &= SCGC_PORTAE_CLK_OFF;
}

/* PLL External Reference Divider values in MCG.C5 */
#define PRDIV0_0 0x0
#define PRDIV0_16 0xF

/* PLL Clock Enable bit in MCG.C5 */
#define PLLCLKEN (1 << 6)

/* PLL Select in MCG.C6 */
#define PLLS (1 << 6)

/* PLL VCO Divide Factor */
#define VDIV0_24 0x0

/* PLL Lock Bit in MCG.S */
#define LOCK0 (1 << 6)

/* Frequency range select encoding in MCG.C2 */
#define RANGE0_HF (1 << 4)
#define RANGE0_VHF (1 << 5)

/* External Reference Select in MCG.C2 */
#define EREFS0 (1 << 2)

/* External Referance Enable bit in OSC0.CR */
#define ERCLKEN (1 << 7)

void initialize_clock(void){
	/* simple clock configuration that involves initializing the SPI so we can get the external clock reference from the transceiver */

	/* set PLL external reference divider (PRDIV0) to 16, this will give us 2 MHz */
	MCG.C5 = PRDIV0_16;

	/* enable MCGPLLCLK if system is in Normal Stop mode */
	MCG.C5 |= PLLCLKEN;

	/* select PLL instead of FLL, multiply signal by 24 to get 48MHz */
	MCG.C6 |= (1 << 6) | VDIV0_24;

	/* wait for PLL lock */
	while(!(MCG.S & LOCK0));

	/* set frequency range select to high frequency range for oscillator
	   and select external reference clock
	*/
	MCG.C2 |= RANGE0_HF | EREFS0;

	/* enable external oscillator */
	OSC0.CR = ERCLKEN;

	/* now enable clock for SPI modules, AGAIN! */
	SIM.SCGC4 |= SCGC_SPI1_CLK | SCGC_SPI0_CLK;

	/* enable clock for all ports */
	SIM.SCGC5 |= SCGC_PORTAE_CLK;

	/* enable clock for TPM, RTC modules */
	//SIM.SCGC6 |= 0x27000000;

	return;
}

/* green LED */
#define PTB1 (1 << 1)

/* red LED */
#define PTB2 (1 << 2)

/* blue LED */
#define PTB17 (1 << 17)

/* alternative function number */
#define pin_disable (0 << 8)
#define alt1 (1 << 8)
#define alt2 (2 << 8)
#define alt3 (3 << 8)
#define alt4 (4 << 8)
#define alt5 (5 << 8)
#define alt6 (6 << 8)
#define alt7 (7 << 8)

void initialize_gpio(void){
	/* procedure for getting the GPIO going on pins PTB1, PTB2, PTB17 */

	/* select alt 1 functionality
	   for PTB1, PTB2, PTB17.
	   Alt 1 functionality is just GPIO
	*/
	PORTB.PCR[1] |= alt1;
	PORTB.PCR[2] |= alt1;
	PORTB.PCR[17] |= alt1;

	/* set data direction as output */
	GPIOB.PDDR |= PTB17 | PTB2 | PTB1;

	/* turn all LEDs of by pulling pins high */
	GPIOB.PTOR = PTB17 | PTB2 | PTB1;

	return;
}

void initialize_uart(void){
	/* UART configuration */
	struct uart_config myUART = {
		/* pin for transmit = PTC4 */
		//.TX = {.port=&PORTC, .pin=4,},

		/* pin for transmit = PTD5 */
		.TX = {.port=&PORTD, .pin=5,},

		/* pin for receive = PTC3 */
		//.RX = {.port=&PORTC, .pin=3,},

		/* pin for receive = PTD4 */
		.RX = {.port=&PORTD, .pin=4,},

		/* baud rate */
		.baud = 9600,
	};
	//uart_init(&UART1, &myUART);
	uart_init(&UART2, &myUART);
}


void initialize_uart0(void){
	/* UART0 configuration */
	struct uart_config myUART = {
		/* pin for transmit = PTA2 */
		.TX = {.port=&PORTA, .pin=2,},

		/* pin for receive = PTA1 */
		.RX = {.port=&PORTA, .pin=1,},

		/* baud rate */
		.baud = 9600,
	};
	uart_init(&UART0, &myUART);
}
#endif

#if 0
void initialize_tpm(void){
  	/* procedure for initializing Timer/PWM module */

	/* Clock mode select for each module, make TPM counter increment on every TPM counter clock */
  	TPM0.SC = 0x8;
	TPM1.SC = 0x8;
	TPM2.SC = 0x8;

	/* more needs to be done here, maybe? */
  	return;
}
#endif

int main(void) {

	/* delay loop for POR, transceiver not available for 10ms */
	for(uint32_t i = 0; i < 1000000; ++i);

	/* call initialization procedures */
	initialize_spi();
	initialize_clock();
	initialize_gpio();

	//initialize_uart();
	initialize_uart0();
	//initialize_tpm();
   	//asm volatile ("cpsie   i");

	/* this function is in transceiver.c if you want more details */
	configure_transceiver(Mode_TX, PAOutputCfg(PA0, 0x1F));

	uint8_t txbyte = 0x55;
	//static uint8_t txbyte[3] = {0x55, 0xD, 0xA};

	uint8_t rxbyte = 0x0;

	while(1) {

		/* test case 1: UART0 module, passed, passes when RDRF not polled as well */
          	uart_write(&UART0, 1, &txbyte);
          	//uart_read(&UART0, 1, &rxbyte);

          	/* test case 2: UART1 module, passed only when RDRF was not polled */
		//uart_write(&UART1, 1, &txbyte);
          	//uart_read(&UART1, 1, &rxbyte);

		/* test case 3: UART2 module, passed only when RDRF was not polled */
		//uart_write(&UART2, 1, &txbyte);
          	//uart_read(&UART2, 1, &rxbyte);

		for(uint32_t i = 0; i < 1000000; ++i);

	       	/* toggle LED connected to PTB2 */
		GPIOB.PTOR = PTB1;

		if(rxbyte == 0x55){
                	GPIOB.PTOR = PTB17;
		}
	}
	return 0;
}

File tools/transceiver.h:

/*
	Transceiver header

	Programmed by William Harrington and Michael Mathis
*/
#include <stdbool.h>
#include <stdint.h>

#include "drivers/spi.h"
#ifndef _TRANSCEIVER_H_
#define _TRANSCEIVER_H_
/* struct declaration for transceiver */
struct TRANSCEIVER {
  	uint8_t RegFifo; /* FIFO read/write access */
  	uint8_t RegOpMode; /* Operating modes of the transceiver */
  	uint8_t RegDataModul; /* Data operation mode and modulation settings */
  	uint8_t RegBitrateMsb; /* bit rate setting, most significant bits */
  	uint8_t RegBitrateLsb; /* bit rate setting, least significant bits */
  	uint8_t RegFdevMsb; /* frequency deviation setting, most significant bits */
  	uint8_t RegFdevLsb; /* frequency deviation setting, least significant bits */
  	uint8_t RegFrfMsb; /* RF carrier frequency, most significant bits */
	uint8_t RegFrfMid; /* RF carrier frequency, Intermediate Bits */
	uint8_t RegFrfLsb; /* RF carrier frequency, least significant bits */
	uint8_t RegOsc1; /* RC Oscillators Settings */
	uint8_t RegAfcCtrl; /* AFC control in low modulation index situations */
	uint8_t RegLowBat; /* Low Battery Indicator Settings */
	uint8_t RegListen1; /* Listen Mode settings */
	uint8_t RegListen2; /* Listen Mode Idle duration */
	uint8_t RegListen3; /* Listen Mode RX duration */
	uint8_t RegVersion; /* RF ID relating the silicon revision */
	uint8_t RegPaLevel; /* PA selection and Output Power control */
	uint8_t RegPaRamp; /* Control of the PA ramp time in FSK mode */
	uint8_t RegOcp; /* Over Current Protection control */
	uint8_t RegLna; /* LNA settings */
	uint8_t RegRxBw; /* Channel Filter BW Control */
	uint8_t RegAfcBw; /* Channel Filter BW control during the AFC routine */
	uint8_t RegOokPeak; /* OOK demodulator selection and control in peak mode */
	uint8_t RegOokAvg; /* Average threshold control of the OOK demodulator */
	uint8_t RegOokFix; /* Fixed threshold control of the OOK demodulator */
	uint8_t RegAfcFei; /* AFC and FEI control and status */
	uint8_t RegAfcMsb; /* MSB of the frequency correction of the AFC */
	uint8_t RegAfcLsb; /* LSB of the frequency correction of the AFC */
	uint8_t RegFeiMsb; /* MSB of the calculated frequency error */
	uint8_t RegFeiLsb; /* LSB of the calculated frequency error */
	uint8_t RegRssiConfig; /* RSSI-related settings */
	uint8_t RegRssiValue; /* RSSI value in dBm */
	uint8_t RegDioMapping1; /* Mapping of pins DIO0 to DIO3 */
	uint8_t RegDioMapping2; /* Mapping of pins DIO4 and DIO5/Clkout frequency */
	uint8_t RegIrqFlags1; /* Status register: PLL Lock state, Timeout, RSSI > Threshold... */
	uint8_t RegIrqFlags2; /* Status register: FIFO handling flags, Low battery detection... */
	uint8_t RegRssiThresh; /* RSSI Threshold control */
	uint8_t RegRxTimeout1; /* Timeout duration between RX request and RSSI detection */
	uint8_t RegRxTimeout2; /* Timeout duration between RSSI detection and PayloadReady */
	uint8_t RegPreambleMsb; /* Preamble length, MSB */
	uint8_t RegPreambleLsb; /* Preamble length, LSB */
	uint8_t RegSyncConfig; /* Sync Word Recognition control */
	uint8_t RegSyncValue1; /* Sync Word byte 1 */
	uint8_t RegSyncValue2; /* Sync Word byte 2 */
	uint8_t RegSyncValue3; /* Sync Word byte 3 */
	uint8_t RegSyncValue4; /* Sync Word byte 4 */
	uint8_t RegSyncValue5; /* Sync Word byte 5 */
	uint8_t RegSyncValue6; /* Sync Word byte 6 */
	uint8_t RegSyncValue7; /* Sync Word byte 7 */
	uint8_t RegSyncValue8; /* Sync Word byte 8 */
	uint8_t RegPacketConfig1; /* Packet mode settings */
	uint8_t RegPayloadLength; /* Payload length setting */
	uint8_t RegNodeAdrs; /* Node address */
	uint8_t RegBroadcastAdrs; /* Broadcast address */
	uint8_t RegAutoModes; /* Auto modes settings */
	uint8_t RegFifoThresh; /* Fifo threshold, TX start condition */
	uint8_t RegPacketConfig2; /* Packet mode settings */
	uint8_t RegAesKey1; /* cypher key, byte 1 */
	uint8_t RegAesKey2; /* cypher key, byte 2 */
	uint8_t RegAesKey3; /* cypher key, byte 3 */
	uint8_t RegAesKey4; /* cypher key, byte 4 */
	uint8_t RegAesKey5; /* cypher key, byte 5 */
	uint8_t RegAesKey6; /* cypher key, byte 6 */
	uint8_t RegAesKey7; /* cypher key, byte 7 */
	uint8_t RegAesKey8; /* cypher key, byte 8 */
	uint8_t RegAesKey9; /* cypher key, byte 9 */
	uint8_t RegAesKey10; /* cypher key, byte 10 */
	uint8_t RegAesKey11; /* cypher key, byte 11 */
	uint8_t RegAesKey12; /* cypher key, byte 12 */
	uint8_t RegAesKey13; /* cypher key, byte 13 */
	uint8_t RegAesKey14; /* cypher key, byte 14 */
	uint8_t RegAesKey15; /* cypher key, byte 15 */
	uint8_t RegAesKey16; /* cypher key, byte 16 */
	uint8_t RegTemp1; /* Temperature Sensor control */
	uint8_t RegTemp2; /* Temperature readout */
	uint8_t RegTestLna; /* Sensitivity boost */
	uint8_t PDSTST3; /* Test register includes PLL bandwidth */
	uint8_t RegTestDagc; /* Fading margin improvement */
	uint8_t RegTestAfc; /* AFC offset for low modulation index AFC */
	uint8_t RegTest; /* Internal test registers */
};

extern struct TRANSCEIVER transceiver;

void configure_transceiver(void);

/*Operating Modes - trans_set_op_mode function
-------------------------------------------------*/
//#define SLEEP_MODE 0
//#define STAND_BY_MODE 1
//#define FS_MODE 2
//#define TRANSMIT_MODE 3
//#define RECEIVE_MODE 4

/*Data Modulation - mode_config struct
-------------------------------------------------*/
//#define PACKET_MODE 0			/*Packet mode*/
//#define CONT_WITH_BIT_SYNC 2	/*Continuous mode with bit sync*/
//#define CONT_WITHOUT_BIT_SYNC 3 /*Continuous mode without bit sync*/

//#define FSK_MODULATION 0
//#define OOK_MODULATION 1

//#define NO_SHAPING 0			
//#define GAUS_BT_1_0	1 /*BT = 1.0*/
//#define GAUS_BT_0_5 2 /*BT = 0.5*/
//#define GAUS_BT_0_3 3 /*BT = 0.3*/
//#define OOK_BR_CUTOFF 1 /*Filtering with freq cutoff = BR*/
//#define	OOK_2BR_CUTOFF 2 /*Filtering with freq cutoff = 2 * BR */

/*Auto Modes - set_automode_*****_cond functions
-------------------------------------------------*/
//#define NONE 0
//#define RISING_FIFONOTEMPTY 1
//#define RISING_FIFOLEVEL 2
//#define RISING_CRCOK 3
//#define RISING_PAYLOADREADY 4
//#define RISING_SYNCADDRESS 5
//#define RISING_PACKETSENT 6
//#define FALLING_FIFONOTEMPTY_ENTER 7

//#define FALLING_FIFONOTEMPTY_EXIT 1

//#define AUTO_SLEEP_MODE 0
//#define AUTO_STAND_BY_MODE 1
//#define AUTO_RECEIVE_MODE 2
//#define AUTO_TRANSMIT_MODE 3

/*
-------------------------------------------------*/

//struct mod_config {
	//uint8_t data_mode; /*2 bits*/
	//uint8_t mod_type; /*2 bits*/
	//uint8_t mod_shaping; /*2 bits*/
//};

/*Page 110 of referenc manual*/
/*
struct listen_config {
	uint8_t idle_time_res;
	uint8_t receive_time_res;
	uint8_t listen_criteria;
	uint8_t listen_end;
	uint8_t idle_coef;
	uint8_t receive_coef;
};
*/

//struct sync_config {
	//uint8_t fifo_fill_cond;
	//uint8_t sync_word_size; /* sync_word_size + 1 bytes */
	//uint8_t sync_error_toleration;
	//uint8_t * sync_word;
//};

/*Page 118 of referenc manual*/
/*
struct packet_config {
	uint16_t preamble_size;
	uint8_t packet_format;
	uint8_t dc_free;
	uint8_t crc_check;
	uint8_t crc_auto_clear;
	uint8_t address_filtering;
	uint8_t payload_length;
	uint8_t node_address;
	uint8_t broadcast_address;
	uint8_t tx_start_cond;
	uint8_t fifo_threshold;
	uint8_t inter_packet_rxdelay;
	uint8_t auto_rx_restart;

};
*/
/*
void read_register(uint8_t address, uint8_t * buffer, uint8_t length);
void write_register(uint8_t address, uint8_t * buffer, uint8_t length);
void trans_set_op_mode(uint8_t mode);
void trans_set_data_mod(struct mod_config * config);
void trans_calibrate_rc(void);
bool trans_read_low_bat(void);
void trans_enable_battery_mon(void);
void trans_disable_battery_mon(void);
*/
/*
000 - 1.695 V
001 - 1.764 V
010 - 1.835 V
011 - 1.905 V
100 - 1.976 V
101 - 2.045 V
110 - 2.116 V
111 - 2.185 V
*/
/*
void trans_set_lowbat_thresh(uint8_t threshold);
void trans_enable_listen(void);
void trans_disable_listen(uint8_t new_mode);
void trans_config_listen(struct listen_config * config);
void trans_set_pa_output(uint8_t power);
*/
//void trans_set_pa_ramp(uint8_t ramp_speed); /*In FSK mode*/
/*
void trans_enable_ocp(void);
void trans_disable_ocp(void);
void trans_set_ocp_trim(uint8_t trim_value);
void trans_enable_aes(void);
void trans_disable_aes(void);
*/
//void trans_set_aes_key(uint8_t * buffer); /*16 bytes*/
/*
void trans_set_automode_enter(uint8_t enter_cond);
void trans_set_automode_exit(uint8_t exit_cond);
void trans_set_automode_intermed(uint8_t intermed_cond);
//cf
//sync
void trans_start_temp_measure(void);
uint8_t trans_read_temp(void);
void trans_set_lna_sensitivity(uint8_t sensitivity);
void trans_set_pll_bandwidth(uint8_t bandwidth);
void trans_set_continuous_dagc(uint8_t dagc);
void trans_set_lowbeta_agc_offset(uint8_t offset);
*/

#endif

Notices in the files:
parts and their libraries:
microbuilder: This work is placed in the public domain, and may be freely used for commercial and non-commercial work with the following conditions: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
SparkFun-v5: Licensing: CC v3.0 Share-Alike You are welcome to use this library for commercial purposes.
